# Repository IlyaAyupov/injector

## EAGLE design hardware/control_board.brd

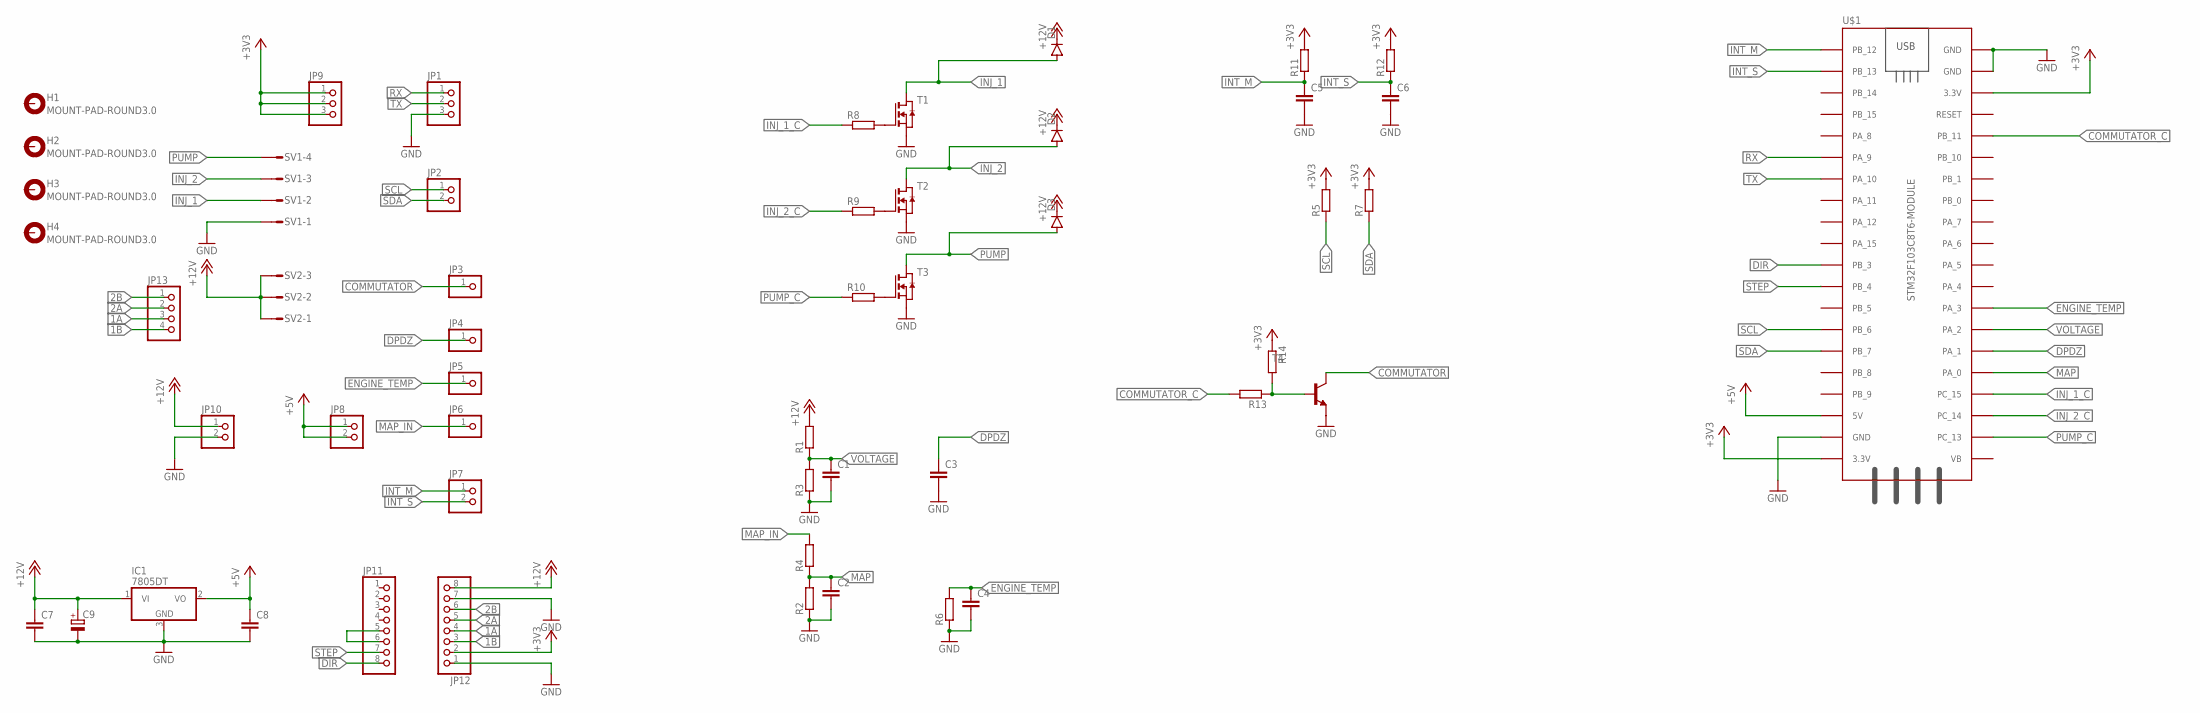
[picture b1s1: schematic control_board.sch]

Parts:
C1, C2, C3, C4, C5, C6, C7, C8: C-EUC1206; C1206
C9: CPOL-EU140CLH-0810; 140CLH-0810
D1, D2, D3: DIODE-SMB; SMB
H1, H2, H3, H4: MOUNT-PAD-ROUND3.0; 3,0-PAD
IC1: 7805DT; TO252
JP1, JP9: PINHD-1X3; 1X03
JP2, JP7, JP8, JP10: PINHD-1X2; 1X02
JP3, JP4, JP5, JP6: PINHD-1X1; 1X01
JP11, JP12: PINHD-1X8; 1X08
JP13: PINHD-1X4; 1X04
R1, R2, R3, R4, R5, R6, R7, R11, R12, R13, R14: R-EU_R1206; R1206
R8, R9, R10: R-EU_R0805; R0805
SV1: MT6-4
SV2: MT6-3
T1, T2, T3: NMOSSOT223; SOT223
T4: BCX54-NPN-SOT89-BCE; SOT89-BCE
U$1: STM32F103C8T6-MODULE

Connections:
1A: JP12.4, JP13.3
1B: JP12.3, JP13.4
2A: JP12.5, JP13.2
2B: JP12.6, JP13.1
+3V3: JP9.1, JP9.2, JP9.3, JP12.2, R5.2, R7.2, R11.2, R12.2, R14.1, U$1.3.3V_1 (3.3V), U$1.3.3V_2 (3.3V)
+5V: C8.1, IC1.2 (VO), JP8.1, JP8.2, U$1.5V
+12V: C7.1, C9.+, D1.C, D2.C, D3.C, IC1.1 (VI), JP10.1, JP12.8, R1.2, SV2.1, SV2.2, SV2.3
COMMUTATOR: JP3.1, T4.C
COMMUTATOR_C: R13.2, U$1.PB_11
DIR: JP11.8, U$1.PB_3
DPDZ: C3.1, JP4.1, U$1.PA_1
ENGINE_TEMP: C4.1, JP5.1, R6.2, U$1.PA_3
GND: C1.2, C2.2, C3.2, C4.2, C5.2, C6.2, C7.2, C8.2, C9.-, IC1.3 (GND), JP1.3, JP10.2, JP12.1, JP12.7, R2.1, R3.1, R6.1, SV1.1, T1.3 (S), T2.3 (S), T3.3 (S), T4.E, U$1.GND_1 (GND), U$1.GND_2 (GND), U$1.GND_3 (GND)
INJ_1: D1.A, SV1.2, T1.2 (D), T1.4 (D)
INJ_1_C: R8.1, U$1.PC_15
INJ_2: D2.A, SV1.3, T2.2 (D), T2.4 (D)
INJ_2_C: R9.1, U$1.PC_14
INT_M: C5.1, JP7.1, R11.1, U$1.PB_12
INT_S: C6.1, JP7.2, R12.1, U$1.PB_13
MAP: C2.1, R2.2, R4.1, U$1.PA_0
MAP_IN: JP6.1, R4.2
unnamed: JP11.5, JP11.6
unnamed: R13.1, R14.2, T4.B
unnamed: R8.2, T1.1 (G)
unnamed: R9.2, T2.1 (G)
unnamed: R10.2, T3.1 (G)
PUMP: D3.A, SV1.4, T3.2 (D), T3.4 (D)
PUMP_C: R10.1, U$1.PC_13
RX: JP1.1, U$1.PA_9
SCL: JP2.1, R5.1, U$1.PB_6
SDA: JP2.2, R7.1, U$1.PB_7
STEP: JP11.7, U$1.PB_4
TX: JP1.2, U$1.PA_10
VOLTAGE: C1.1, R1.1, R3.2, U$1.PA_2

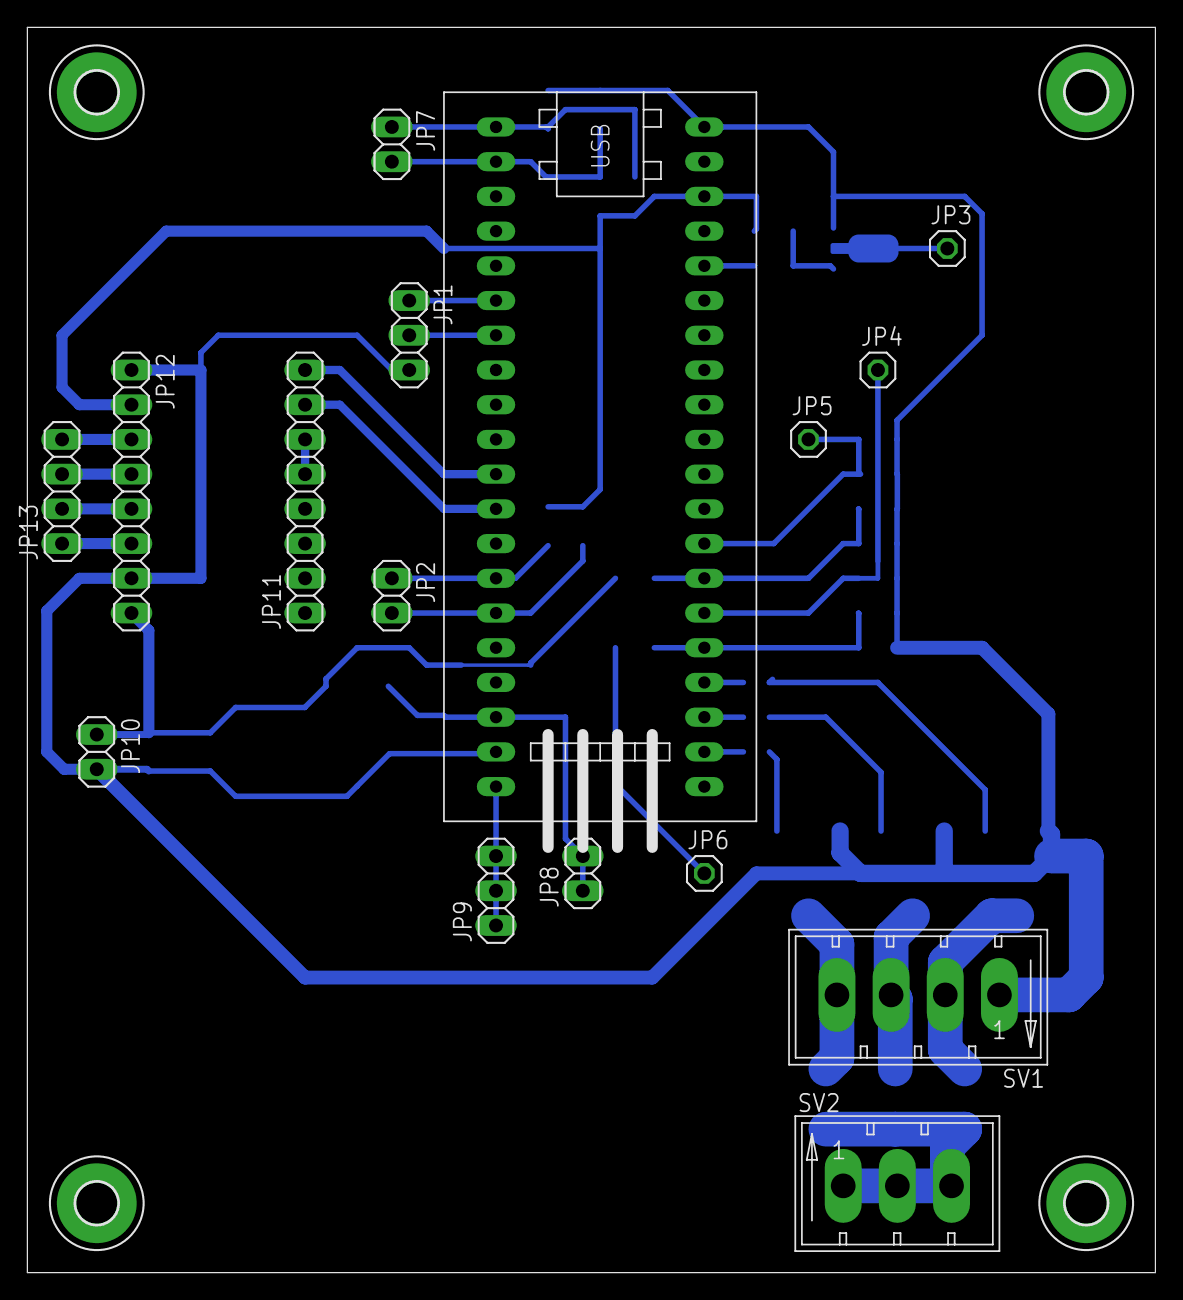
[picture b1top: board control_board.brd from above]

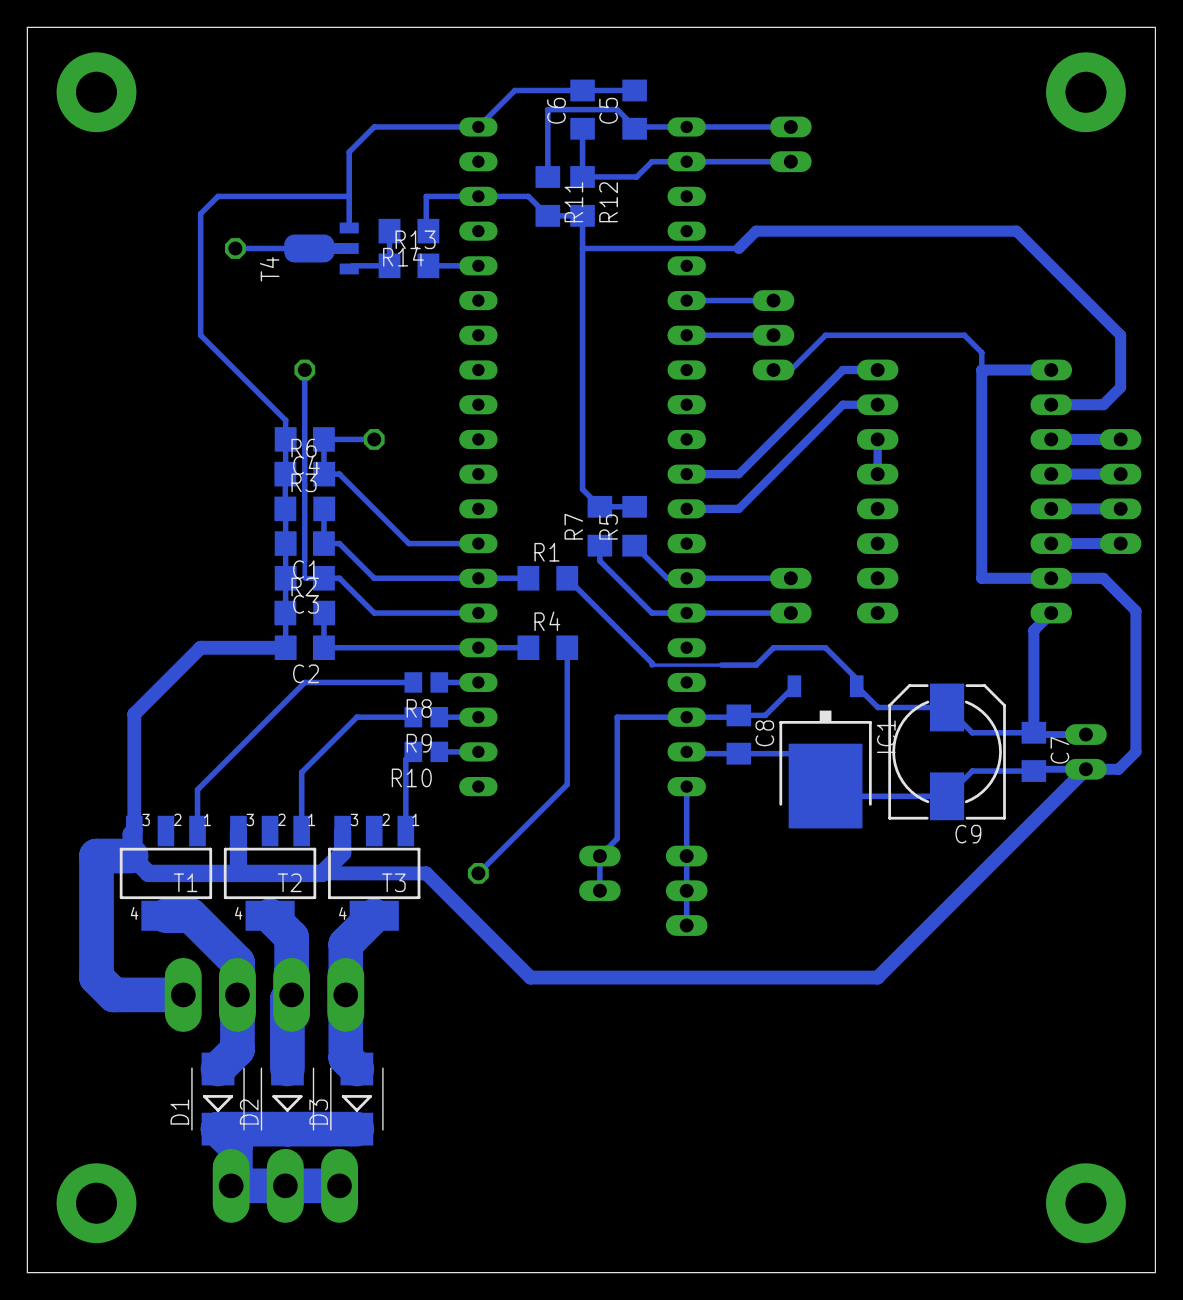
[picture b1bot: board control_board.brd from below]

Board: 2 copper layers, 82.5 x 91.1 mm, 51 parts (31 on the bottom side), 34 nets.

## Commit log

2020-09-04 docs added
